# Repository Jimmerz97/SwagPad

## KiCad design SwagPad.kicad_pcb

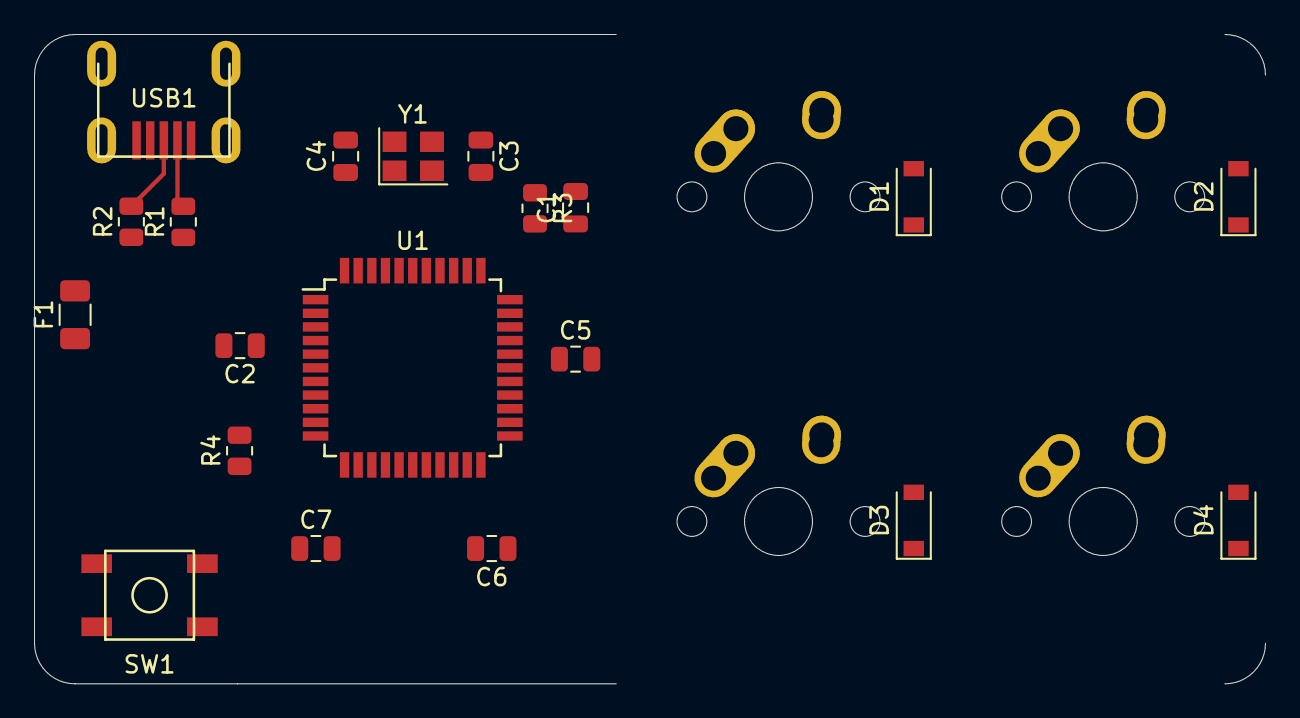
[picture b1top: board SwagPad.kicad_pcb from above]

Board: 2 copper layers, 72.2 x 38.1 mm, 24 parts (0 on the bottom side), 20 nets.

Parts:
C1, C2, C6: 0.1uF; C_0805_2012Metric
C3, C4: 22pF; C_0805_2012Metric
C5: 1uF; C_0805_2012Metric
C7: 10uF; C_0805_2012Metric
D1, D2, D3, D4: D_Small; D_SOD-123
F1: 500mA; Fuse_1206_3216Metric
MX1, MX2, MX3, MX4: MX-NoLED; MX-1U-NoLED
R1, R2: 22; R_0805_2012Metric
R3, R4: 10k; R_0805_2012Metric
SW1: SW_Push; SKQG-1155865
U1: ATmega32U4-AU; TQFP-44_10x10mm_P0.8mm
USB1: Molex-0548190589
Y1: 16MHz; Crystal_SMD_3225-4Pin_3.2x2.5mm

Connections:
+5V: C1.1, C2.1, C6.1, C7.1, F1.1, R3.1, U1.2, U1.7, U1.14, U1.24, U1.34, U1.44
COL0: MX1.1, MX2.1, U1.29
COL1: MX3.1, MX4.1, U1.28
D+: R2.2, USB1.3
D-: R1.2, USB1.4
GND: C1.2, C2.2, C3.2, C4.2, C5.2, C6.2, C7.2, R4.1, SW1.1, U1.5, U1.15, U1.23, U1.35, U1.43, USB1.1, Y1.2, Y1.4
unnamed: C3.1, U1.17, Y1.1
unnamed: C4.1, U1.16, Y1.3
unnamed: C5.1, U1.6
unnamed: D1.2, MX1.2
unnamed: D2.2, MX2.2
unnamed: D3.2, MX3.2
unnamed: D4.2, MX4.2
unnamed: R1.1, U1.3
unnamed: R2.1, U1.4
unnamed: R3.2, SW1.2, U1.13
unnamed: R4.2, U1.33
ROW0: D1.1, D3.1
ROW1: D2.1, D4.1, U1.30
VCC: F1.2, USB1.5

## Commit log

2021-05-12 Add submodules
2021-05-12 SwapPad
    3x3 + 1 + Enc + Knob + Wireless
2021-05-13 Pcb Made
    BossPad
2021-05-13 PCB
    BossPad
